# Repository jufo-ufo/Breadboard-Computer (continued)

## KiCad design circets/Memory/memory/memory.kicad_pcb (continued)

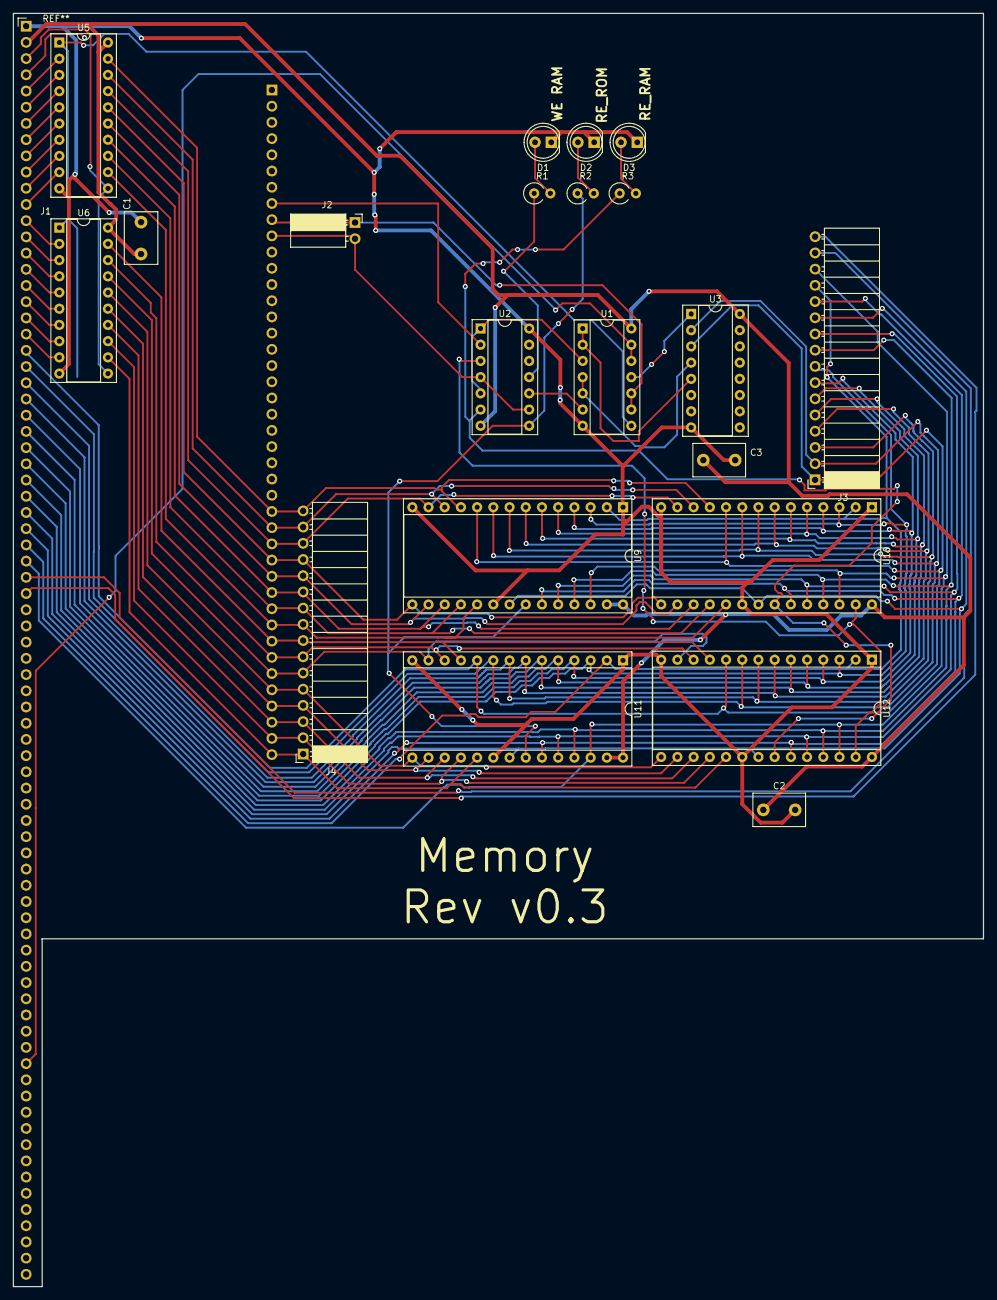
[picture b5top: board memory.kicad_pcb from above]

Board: 2 copper layers, 152.0 x 199.5 mm, 23 parts (1 on the bottom side), 68 nets.

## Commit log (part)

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2021-09-18 Added Output PDF
2021-09-18 Restructured Repository!
2021-09-18 Moved some legacy images to images lol
2021-09-18 Removed old Project files
2021-09-19 Added Supervisor Mode, Memory Map und Stack
2021-09-19 Added PEEK, BKS1 and BKS2
2021-09-23 It's a badly formatted text File
    It's a badly formatted text File of what I thought of for an I/O Connection/Protocol
2021-09-23 Added Version Number
2021-09-23 Build second version of ROM-Programmer
2021-09-23 Of Course you need a Clock
    Added a Clock Pin to both Connector-Variants
2021-09-28 Renamed File, Applyed Corrections Added Ins-Set
2021-09-30 Added FPGA-toolchain to gitignore and setup folder, nothing more lol
2021-10-02 made ToDo-List more specific, primarily with "write Specification"
2021-10-02 addet files generated by pycharm to .gitignore
2021-10-02 moved IO_Protocoll_v1.txt to a WIP Folder, that doesn't get committed.
2021-10-02 It's the 2nd version of the LaTeX Specification but the 4th we have here on Github (including the two we have as .txt)
2021-10-02 Typo
2021-10-02 first(unfinished) attempt to update the Input/Output Definition
2021-10-02 Reworked Interrupts
2021-10-02 trying to successfully add the WIP-Folder to the .gitignore
2021-10-02 Renamed Documentation
2021-10-02 README corrected
2021-10-02 corrected Typo
2021-10-02 WE DON'T NEED IT!!!
2021-10-02 improved I/O-Instruction Names
2021-10-03 added I/O-Instructions
2021-10-03 trying to fix table arrangement
2021-10-05 don't know waht chanced, but something changed
2021-10-05 this shouldn't be here
2021-10-05 trying th get the WPI-Folder out of Github!!!
2021-10-05 I DON'T WANT CONFIG FILES TO BE UPLOADED!
2021-10-05 don't know why its there, but I can't get rid of it in the "open Commits" sector IT ANOYS ME
2021-10-05 don't have any clue what changed in this FIle, because I only copied a link from it, but I don't care...
2021-10-05 Added XOR-, OR- and AND- Gates to parts index
2021-10-06 Build Data Collection Scripts
2021-10-07 Added option external test signal + split output
2021-10-07 Added support for external signal source
2021-10-08 first complete version of the IO-Documentation
2021-10-09 Statusupdate - README.md
2021-10-09 Removed old and outdated section titles
2021-10-09 fix missing Permission-part
2021-10-14 Update Parts index with XOR, OR and AND
2021-10-14 Fixed Line formating
2021-10-17 Remove toolchain form .gitignore
2021-10-17 Added Docker Contrainer for Running VTR-Toolchain + Added Test Circet
2021-10-17 Added Documentation + Coolred Terminal in Container
2021-10-22 Moved HandBuch into a seperate folder + Added tex byproducts to gitignore
2021-10-29 Messured some chips
2021-10-30 Added Images from open CD4096
2021-10-30 Added FLASH and SMD to DIP Adapter to part index
2021-11-03 Got basic form of VTR to work \0/
2021-11-04 Added doc about how to start gui in docker container
2021-11-04 Added test circet
2021-11-04 Setup CLion-Even for an assembler
2021-11-05 Corrected Spelling Mistakes until Kontrollfluss and add Athimatik Operations Sektion
2021-11-05 Small Edits, misc stuff
2021-11-11 Removed spelling mistakes until IO, Added RET and CALL to Stack Section, Added small bits here and there
2021-11-13 Fixed small errors and in consistencis
2021-11-15 Added new propagation-delay analysis script
2021-11-15 Added messurments for (mostly) all OR, AND, XOR and NAND-Gates
2021-11-16 Removed invalid test + Replaced the with new + Added some missing ones
2021-11-16 Added no ploting option and fixed bug with displaying delays
2021-11-16 Added delays to part index
2021-11-18 Started writting with Assembler
2021-11-18 Corrections, Added Supvisor comment, rewrote Interrupts, restructured
2021-11-18 Removed old assembler files and added Jetbrains config folder to gitignore
2021-11-18 Added Test PCB-Layout
2021-11-18 Added Table for Recording PCB manufacturing
2021-11-22 Reset all assembler files
2021-11-25 Changen Memory Layout around for more convinient hardware implementation
2021-12-06 Did Stuff, don't know, edit this shit ~2 weeks ago
2021-12-06 Added New Datapoints to PCB etching!
2021-12-06 Fixed wrong connection in test circet
2021-12-06 Added Architecture Drawing!
2021-12-06 Added Component Libary for kiCad
2021-12-06 Added first drawing of the Register file
2021-12-08 Build new framework for testing PD and other stuff
2021-12-09 Build small script to save oscilloscope and added abient temp to temp
2021-12-09 Added NAND-PD-Tests and Programmer Manual
2021-12-09 Build Schematics for AM
2021-12-09 Added custome IC and there footpit
2021-12-09 Added AM to Architecure
2021-12-09 sorry, but wtich looks awfull
2021-12-09 Can't chanche brank without merging
2021-12-09 Fixed typo (TM not MT) in spec
2021-12-09 Completed Schematic Drawing \0/
2021-12-09 File chanched, so have to commit!
2021-12-13 Created Updated version of scemeatic
2021-12-13 ... and updated PDF too...
2021-12-15 Updated Schematic!
2021-12-16 Started Rework on AM
2021-12-17 Created Test Circet pdf
2021-12-17 Updated PCB-Dataset with old test
2021-12-19 Added Multiplexers to Part index
2021-12-19 Fixed Small Issues after build Protype
2021-12-20 Added Image of Activation Module + Removed 2 Activation Modules from Schematic
2021-12-21 Added Pin Headers to part index
2021-12-21 Made Footprint for 74HC541 and started Footprint for Bus Connector
2021-12-23 New Attempt to build an assembler. Implement Lexer
2021-12-26 Transfored Repo to new computer, alot has apperntly chande, let's commit it all!
2021-12-27 fixing my pull issues
2021-12-27 Finally uploading my chances successfully
2021-12-27 sorry hd to fix some spelling mistakes
2021-12-27 a little more spelling-correction
2021-12-27 Reworked Register Logic-Schematic and Kicad-Schematic
2021-12-27 Added Decoder to part index
2021-12-28 added Table for Parts
2021-12-28 tested Table for Parts
2021-12-28 completed Table for Parts
2021-12-28 Cleand up circet folder
2021-12-28 Added Colums to TODO List
2021-12-28 Fixed Issue with wrong pins in activation Module!
2021-12-28 Adjusted Prices for Full Addre in part index
2021-12-28 Build Logic Schematic for Bank, Bank Controller and BID-Register
2021-12-29 Build Schmatic for Memory Circet
2021-12-30 Added .swps and all .idea and .vscode folders/files to gitignore
2021-12-30 Build Schematic for Timer
2021-12-31 corrected a little bit (not compiled to pdf)
2021-12-31 added LogiSim Plan for most do the ALU-Functionality
2021-12-31 My Idea of our "Langfassung"
2022-01-01 Minor Correction for Timed Interrupt and comment on it
2022-01-01 Corrected some spelling mistakes
2022-01-02 reworked IO (not finished)
2022-01-02 improved TEST-Instruction Circuit
2022-01-02 If we have a .xml file uploadet, it should be usable
2022-01-02 big spelling-overhaul
2022-01-02 Build Schematic for Memory
2022-01-02 Replaced arg with op in HandBuch
2022-01-02 added comment about IO-IDs
2022-01-02 Some Minor Corrections
2022-01-02 test
2022-01-02 Schamtic for Bank Modules
2022-01-02 Build Schematics for Bank Controller + minor optimaization to eliminat a NAND from Bank Modules
2022-01-03 Analysed Propagation Delay Data for NANDs
2022-01-03 6 Pages "Langfassung" without any content
2022-01-04 Started Building Assembler; Need an clear schceam for encoding instructions
2022-01-04 Added Pictures v2
2022-01-04 Fixed alot of Issues in Memory Module
2022-01-04 Removed BID Register to Replace with Dual Register
2022-01-05 Added correct connectors to AM
2022-01-05 Build Schematic for Dual Register
2022-01-05 Edit arch.drawio to better represent Activation Modules
2022-01-05 Split overflow flags for ADD and SUB
2022-01-06 Renamed Pictures
2022-01-07 Added Columon Etcher to README todo
2022-01-07 Added Pictures
2022-01-07 Fixed ^16 issues
2022-01-07 Fixed spelling mistake
2022-01-08 addet Pictures (with issues)
2022-01-08 Finsihed main structur of assembler!
2022-01-09 addet Pictures
2022-01-09 some progress with the Langfassung (now at 9 Pages)
2022-01-09 some progress with the Langfassung (now at 10 Pages)
2022-01-10 some progress with the Langfassung (now at 11 Pages)
2022-01-10 Removed OFsub Flag
2022-01-10 some progress with the Langfassung (still 11 Pages)
2022-01-10 Added Screanshot of assembler src code
2022-01-10 Added Picutures of PCBs
2022-01-10 some progress with the Langfassung (now with 12 Pages)
2022-01-10 Added Pictures of Activation Module Suff
2022-01-10 V1!!!
2022-01-10 V1.01!!!
2022-01-10 Added Pictures of Memory-Map
2022-01-11 V1.03!!!
2022-01-12 Build PCB Layout for dual Register
2022-01-13 Enlarge Via Size
2022-01-13 Create Manufacor-sheet
2022-01-14 V1.1!!!
2022-01-15 V1.11!!!
2022-01-16 V1.13!!!
2022-01-16 Added Screenshot of Memory Map
2022-01-16 Corrected some minor issues in Langfassung
2022-01-16 Removed 74HC541-Footprint + Added large PinHeaders Footprints
2022-01-16 trust me I'm a engieener wtf just happend here!
2022-01-16 Started Creating Activation Module PCB
2022-01-16 I don't have a fucking clue what these file have to do with my projekt, but git prevents me from getting my job done if I don'T commit these files, so I guess... let's do it
2022-01-16 V1.14!!!
2022-01-16 V1.15!!!
2022-01-16 V1.16git status! FINISH ITgit statusgit statusgit status
2022-01-18 Some stuff got deleted in 7d75910a381de5569ad295213d585ff5d338c049 so I added it back in!
2022-01-18 Recompiled Handbuch
2022-01-19 First real attempt to etch a PCB
2022-01-19 Aborting commit due to empty commit message.
2022-01-19 Pls I'm tired
2022-01-25 Deleted irrelevent images for good
2022-01-25 Added Angle and Power for old UV-Lamp
2022-01-25 Deleate another set of irrelvent pictures
2022-01-25 Build Emulator and did other crap
2022-01-25 Added Transiver and PCB-Base Material to Part Index
2022-01-27 Made Todo List fo the presentation
2022-01-27 Added next etching atemt to list
2022-01-27 Reworked PCB Layout for Dual Register
2022-01-27 Wrote Small Script to messuer exposure time
2022-01-27 Build Interrupt Contoller!
2022-01-27 Futher Advanced Progress in build PCB Layout for AM
2022-01-27 Deleated Some auto saves from dual registers
2022-01-27 typo I guess
2022-01-29 Added Etching Attemt Dual Register rev.5 to PCB-Data
2022-01-29 Package ALU into logisim circet
2022-01-29 Added Schemtaic of Instruction Decoder
2022-01-29 Added Plan for Presentation
2022-01-29 Removed Jetbrains config folder
2022-01-30 Added images of Dual Register PCBs
2022-01-30 Added images of Dual Register PCBs Part 2
2022-02-04 Removed Logisim Backup-files
2022-02-04 Gernerated Instruction ROMs
2022-02-04 Created unified ALU-Schmatic
2022-02-04 Renamed Schematics to prevent logisim from complaiing about filenames
2022-02-04 Build Test Programm
2022-02-04 Changed Instruktion Coding to work with Architecture
2022-02-04 Build Logic-Schematic for a simplifyed version of the computer! The answere is 42!
2022-02-04 Updated TODOs
2022-02-09 Added push, pop, call and ret to computer
2022-02-09 Added Images of Propergation Delay testing
2022-02-09 Build Register File PCB-Layout
2022-02-09 Messured PD for Buffer and Octal-D-Latch
2022-02-09 Update Instruction Set due to changes in instruction decoder
2022-02-09 Added 3D-Picture of Register File
2022-02-09 Added LED-Bar
2022-02-09 Added images of schematics
2022-02-09 Did something to part index
2022-02-10 Build first Presentation
2022-02-10 Removed Backups from Action Modules
2022-02-12 RedesignedPCB Layout for Activation Module
2022-02-12 Did **Something** to the file by apperently not editing it, idk
2022-02-12 Removed KiCad Backup for good!
2022-02-12 Added 3D Modle of Action Module
2022-02-12 Added Image of AM PCB-Layout
2022-02-12 fixing merge problems
2022-02-12 improved routing and checkt design
2022-02-13 Change P
2022-02-14 Converted 78 Pinhead from Horzintal to Vertical
2022-02-14 Added gerber files to Activation Module and corrected PinHeader
2022-02-14 Did something to Dual Register idk
2022-02-14 Added Name to Module and Removed old schematic pdfs
2022-02-14 Added Name and other notest to AM PCB-Layout
2022-02-14 Removed/Moved old files belonging to the Dual Register
2022-02-16 Added Siwas Register File PCB + compleateted it!
2022-02-16 fixed all design-issues in register_file
2022-02-16 started planing ALU
2022-02-21 Changed Label on Register File
2022-02-22 Added Osc config for Logic Gate Messurments
